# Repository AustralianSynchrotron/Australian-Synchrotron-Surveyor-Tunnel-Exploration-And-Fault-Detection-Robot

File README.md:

Australian-Synchrotron-Surveyor-Tunnel-Exploration-And-Fault-Detection-Robot
=======

Australian Synchrotron Tunnel Bot

###Requirements
------------

1. Python 2.7.x
2. ZeroMQ 3.2.x
3. pyzmq  13.1.0
4. Pyserial
5. libphidget LATEST (currently 2.1.8.20130723)
6. libusb 1.0-0
7. mjpg-streamer experimental
8. cherrypy 3.2.x
9. Arduino 1.5
-- PS2X by Bill Porter
10. supervisor 3.0b2-1
11. ROOter Huntsman 2014-01-25red

###Changes
-------

ipc doesn't seem to be working on this current configuration (except for LCD screen) so motors and IR Sensors using zmq on tcp://127.0.0.2
ports:
irsensor 127.0.0.2:1000
motors 127.0.0.2:1100

note: srv_motor.py now has the bind command for the motors zmq socket, since it is the service which is always running. If testing run py script with sudo

###Command Line
--------

ssh to odroid. The following command line scripts can be used for some low level control of ass-bot

**move** *\<direction\> \<duration\> \<speed\>*

* direction: forward (f), back (b), left (l), right (r)

* duration: time of movement in seconds

* speed: percentage of max speed. From 1 to 100

**shaft** *\<direction\> \<duration\>*

* direction: up (u) or down (d)

* duration: time of movement in seconds

**camera** *\<direction\> \<PWM duration\>*

* direction: Pan (p) or tilt (t)

* PWM duration: Pulse width from 500 to 2500. Form tilt centre value is 900, for pan centre value is 1500

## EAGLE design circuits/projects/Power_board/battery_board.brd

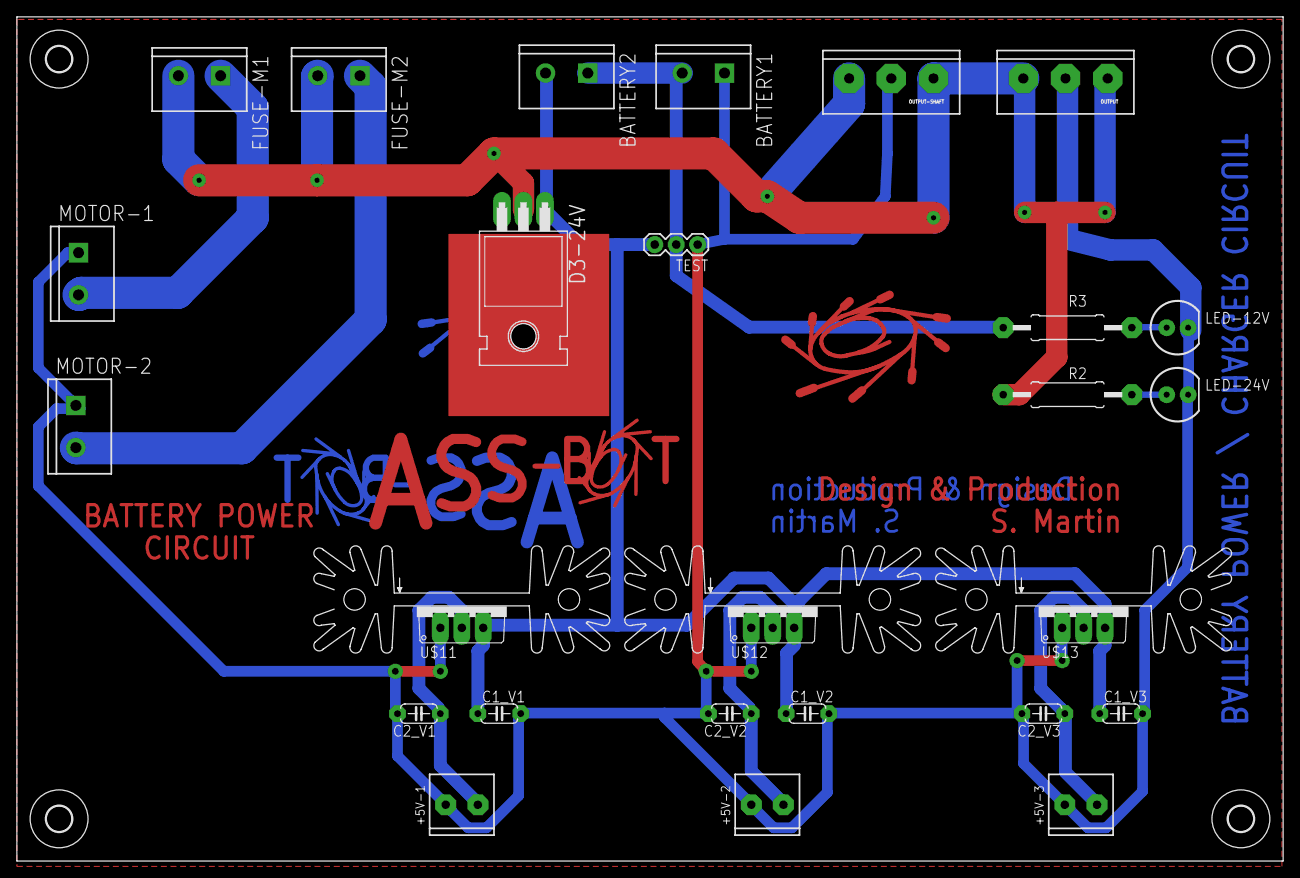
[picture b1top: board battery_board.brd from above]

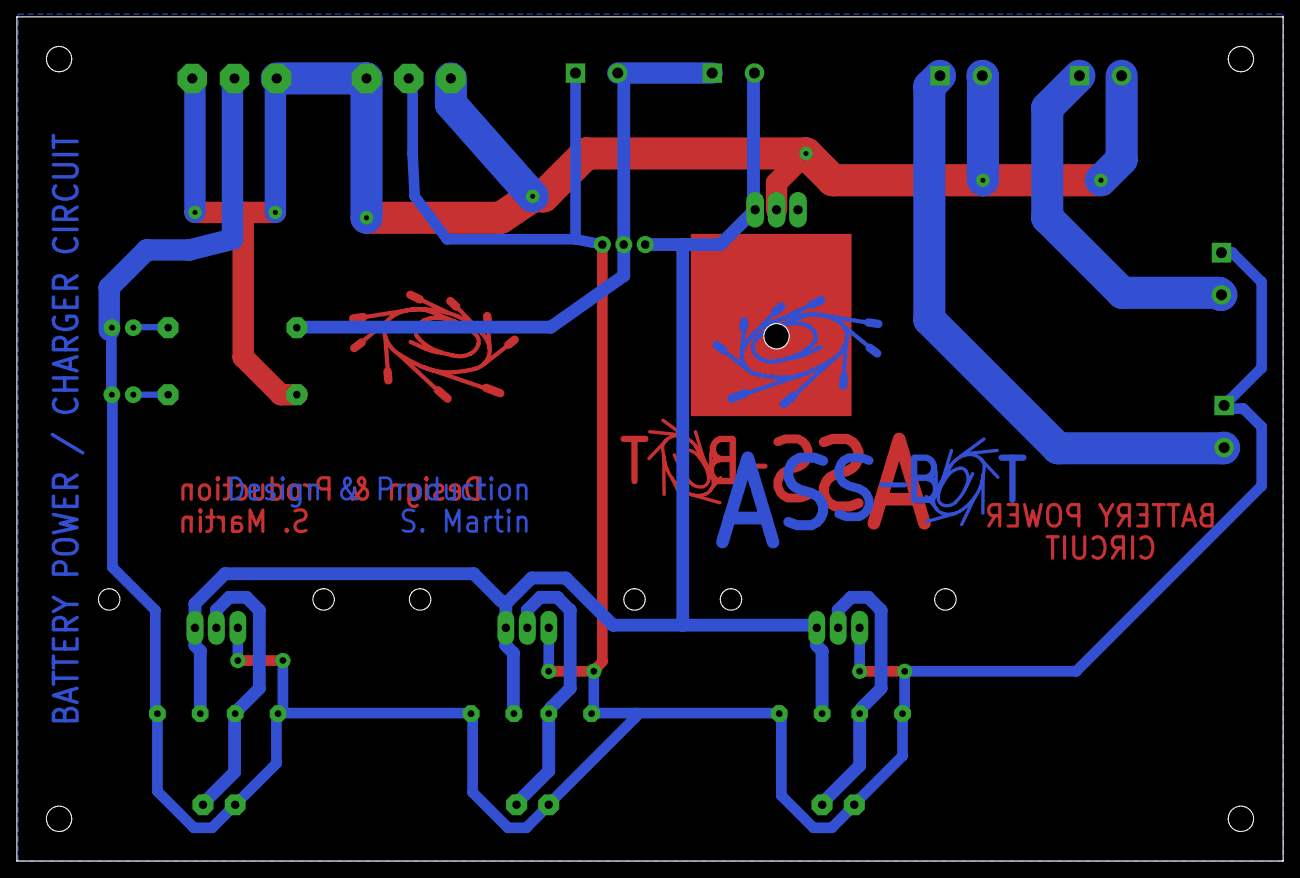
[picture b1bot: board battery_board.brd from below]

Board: 2 copper layers, 150.0 x 100.0 mm, 36 parts (2 on the bottom side), 11 nets.

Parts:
+5V-1, +5V-2, +5V-3: 2-HOLESSC3.81MM; SCREWTERMINAL-3.81MM
BATTERY1, BATTERY2: 12V; SCREWTERMINAL-5MM-2
C1_V1, C1_V2, C1_V3: 2.2uF; C050-024X044
C2_V1, C2_V2, C2_V3: 10uF; C050-024X044
D3-24V: 30A; TO22-DIODE-H
FUSE-M1, FUSE-M2: 3A; SCREWTERMINAL-5MM-2
LED-12V, LED-24V: LED5MM
MOTOR-1, MOTOR-2: 2-HOLESSC5MM; SCREWTERMINAL-5MM-2
OUTPUT: 3-HOLE; SCREWTERMINAL-5MM-3@1
OUTPUT-SHAFT: 3-HOLE; SCREWTERMINAL-5MM-3@1
R2: 1k; 0309/15
R3: 560R; 0309/15
TEST: 1X03
U$1, U$8: LOGO-SYNCHROTRON
U$2: LOGO-ASSBOT-SILK
U$3, U$4, U$5, U$6: 3,0
U$7, U$9: LOGO-ASSBOT
U$10: LOGO-SYNCHROTRON-SILK
U$11, U$12, U$13: LD1085_3A-VREG; TO220V-HEATSINK2

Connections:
12V: BATTERY2.2, C1_V1.1, C1_V2.1, C1_V3.1, D3-24V.P$1, TEST.3, U$11.3, U$12.3, U$13.3
24V: D3-24V.P$2, FUSE-M1.2, FUSE-M2.2, OUTPUT.1, OUTPUT.3, OUTPUT-SHAFT.1, OUTPUT-SHAFT.3, R2.1
GND: +5V-1.1, +5V-2.1, +5V-3.1, BATTERY1.1, C1_V1.2, C1_V2.2, C1_V3.2, C2_V1.2, C2_V2.2, C2_V3.2, LED-12V.K, LED-24V.K, MOTOR-1.1, MOTOR-2.1, OUTPUT.2, OUTPUT-SHAFT.2, TEST.1, U$11.1, U$12.1, U$13.1
unnamed: LED-24V.A, R2.2
unnamed: BATTERY1.2, BATTERY2.1, R3.1, TEST.2
unnamed: +5V-3.2, C2_V3.1, U$13.2
unnamed: FUSE-M2.1, MOTOR-2.2
unnamed: FUSE-M1.1, MOTOR-1.2
unnamed: LED-12V.A, R3.2
unnamed: +5V-2.2, C2_V2.1, U$12.2
unnamed: +5V-1.2, C2_V1.1, U$11.2

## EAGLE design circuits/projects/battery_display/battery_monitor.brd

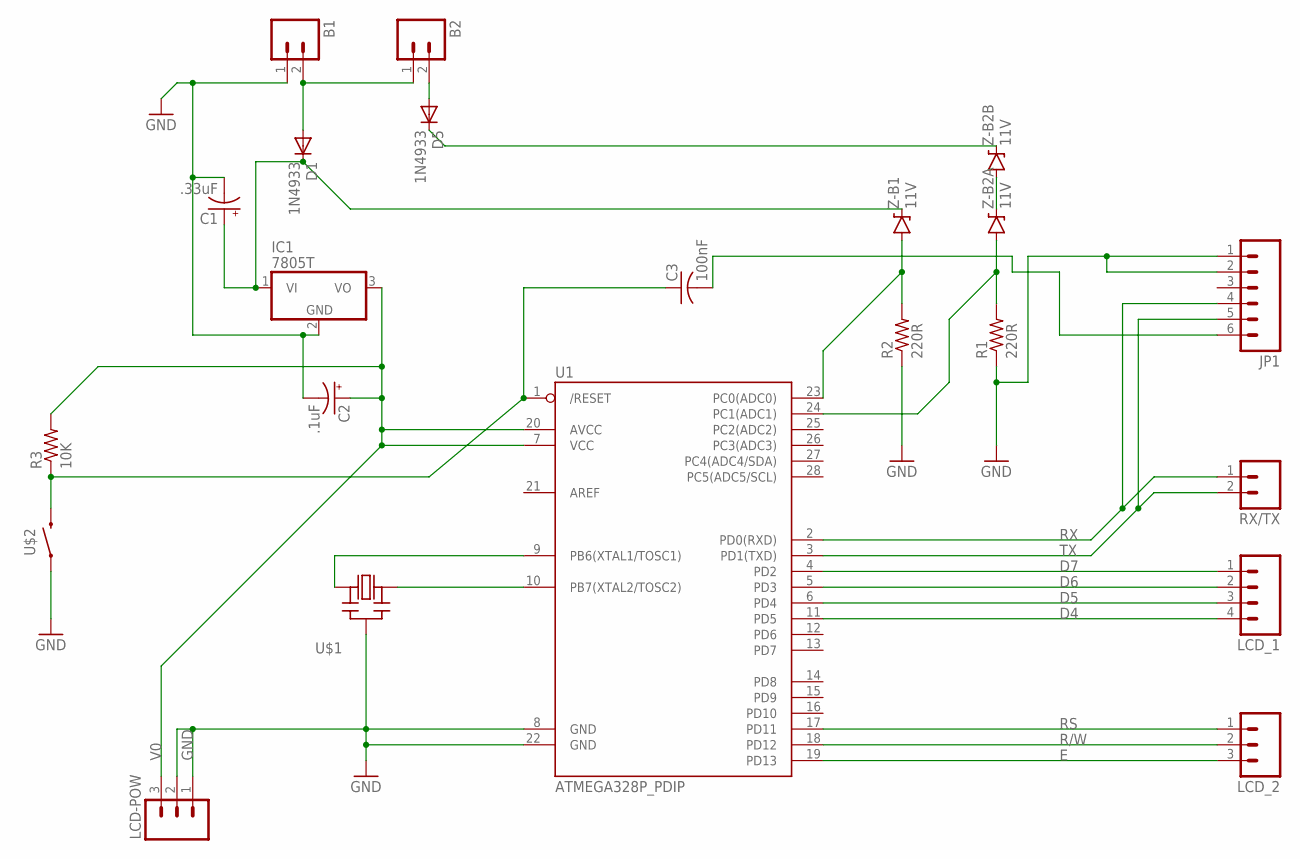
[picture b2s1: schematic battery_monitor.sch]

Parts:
B1, B2: 2-HOLES2-HOLES-5.08MM; 2-HOLES_BIG
C1: .33uF; E2,5-5
C2: .1uF; E2,5-5
C3: 100nF; C050-025X075
D1, D5: 1N4933; DO41-10
IC1: 7805T; TO220H
JP1: M06LONGPADS; 1X06_LONGPADS
LCD-POW: M03PTH; 1X03
LCD_1: M04PTH; 1X04
LCD_2: M03PTH; 1X03
R1, R2: 220R; 0207/10
R3: 10K; 0207/10
RX/TX: M02PTH; 1X02
U1: ATMEGA328P_PDIP; DIL28-3
U$1: OSCILLATOR-THM; CERM_OSC
U$2: SWITCH-MOMENTARY4MM; TACTILE_SWITCH_SMD
Z-B1, Z-B2A, Z-B2B: 11V; DIODE-ZENER

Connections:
D4: LCD_1.4, U1.11 (PD5)
D5: LCD_1.3, U1.6 (PD4)
D6: LCD_1.2, U1.5 (PD3)
D7: LCD_1.1, U1.4 (PD2)
E: LCD_2.3, U1.19 (PD13)
GND: B1.1, C1.-, C2.-, IC1.2 (GND), JP1.1, JP1.2, LCD-POW.1, LCD-POW.2, R1.1, R2.1, U1.8 (GND), U1.22 (GND), U$1.P$2 (GND), U$2.1, U$2.2 (1)
unnamed: U1.10 (PB7(XTAL2/TOSC2)), U$1.P$3 (OUT)
unnamed: U1.9 (PB6(XTAL1/TOSC1)), U$1.P$1 (IN)
unnamed: B1.2, B2.1, D1.A
unnamed: C1.+, D1.C, IC1.1 (VI), Z-B1.P$1 (C)
unnamed: Z-B2A.P$1 (C), Z-B2B.P$2 (A)
unnamed: C3.1, R3.1, U1.1 (/RESET), U$2.3 (2), U$2.4 (2)
unnamed: C3.2, JP1.6
unnamed: R2.2, U1.23 (PC0(ADC0)), Z-B1.P$2 (A)
unnamed: R1.2, U1.24 (PC1(ADC1)), Z-B2A.P$2 (A)
unnamed: D5.C, Z-B2B.P$1 (C)
unnamed: B2.2, D5.A
R/W: LCD_2.2, U1.18 (PD12)
RS: LCD_2.1, U1.17 (PD11)
RX: JP1.4, RX/TX.1, U1.2 (PD0(RXD))
TX: JP1.5, RX/TX.2, U1.3 (PD1(TXD))
V0: C2.+, IC1.3 (VO), LCD-POW.3, R3.2, U1.7 (VCC), U1.20 (AVCC)

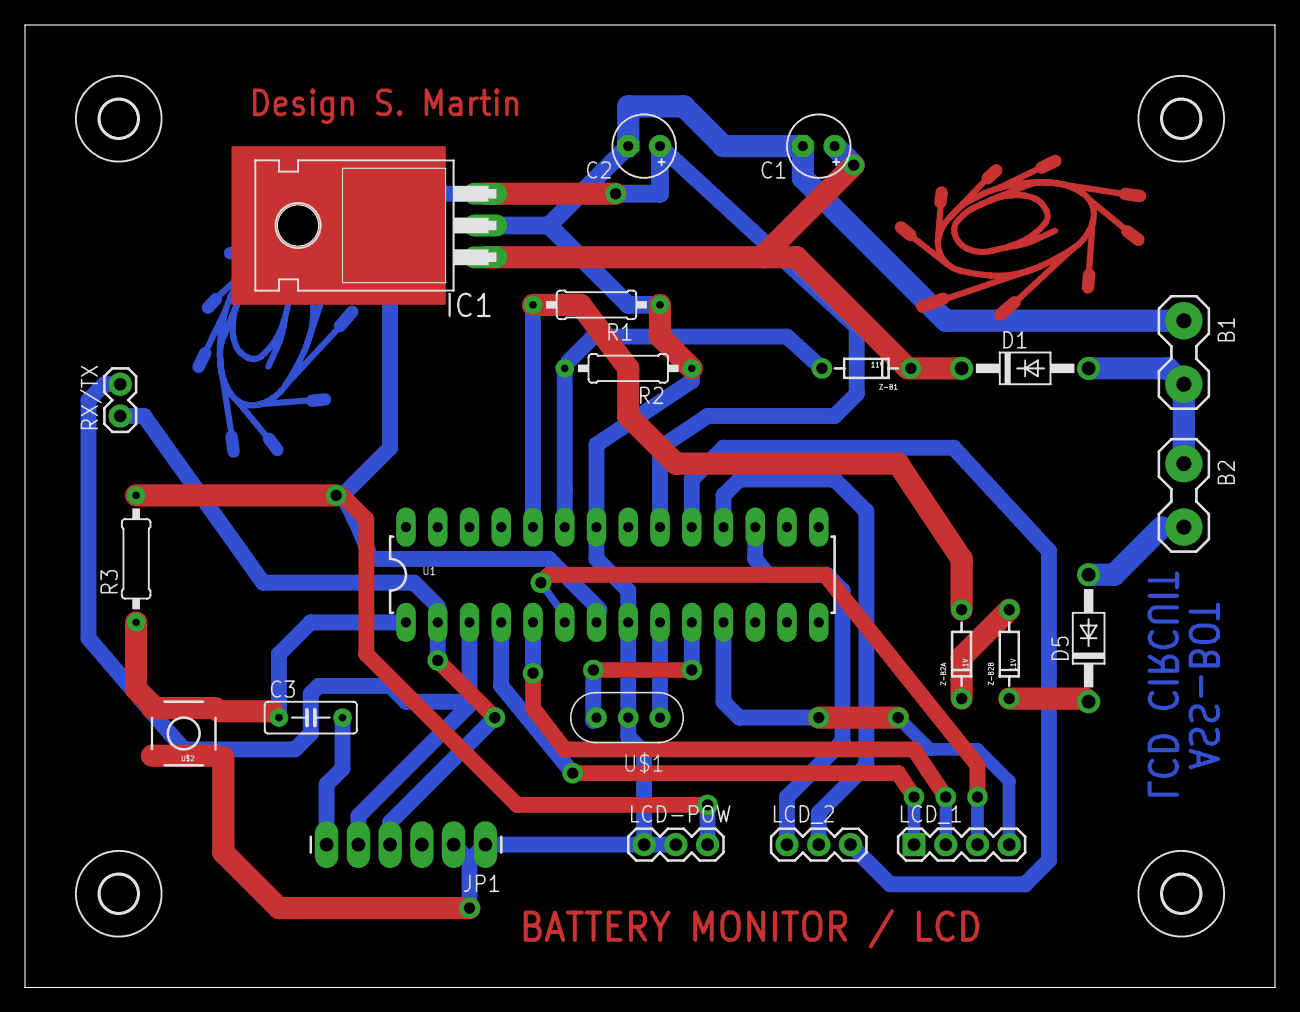
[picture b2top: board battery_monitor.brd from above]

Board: 2 copper layers, 100.0 x 77.0 mm, 28 parts (1 on the bottom side), 22 nets.

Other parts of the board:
U$3, U$4, U$5, U$6: 3,0
U$7, U$8: LOGO-SYNCHROTRON

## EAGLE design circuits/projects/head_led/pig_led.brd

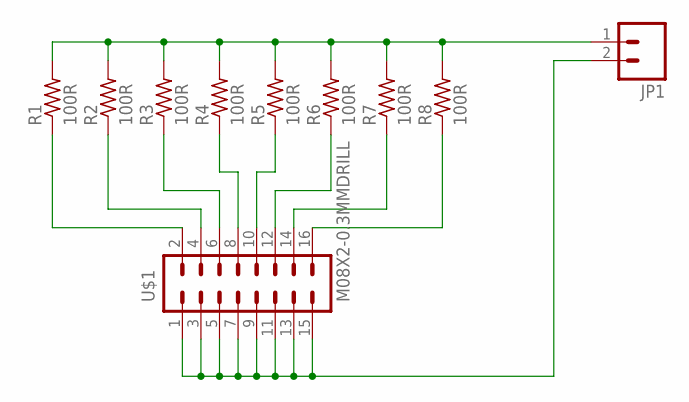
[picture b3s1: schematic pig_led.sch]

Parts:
JP1: M023.5MM; SCREWTERMINAL-3.5MM-2
R1, R2, R3, R4, R5, R6, R7, R8: 100R; 0207/10
U$1: M08X2-0.3MMDRILL; 2X8

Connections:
GND: JP1.2, U$1.1, U$1.3, U$1.5, U$1.7, U$1.9, U$1.11, U$1.13, U$1.15
unnamed: R1.1, U$1.2
unnamed: R2.1, U$1.4
unnamed: R3.1, U$1.6
unnamed: R4.1, U$1.8
unnamed: R5.1, U$1.10
unnamed: R6.1, U$1.12
unnamed: R7.1, U$1.14
unnamed: R8.1, U$1.16
VCC: JP1.1, R1.2, R2.2, R3.2, R4.2, R5.2, R6.2, R7.2, R8.2

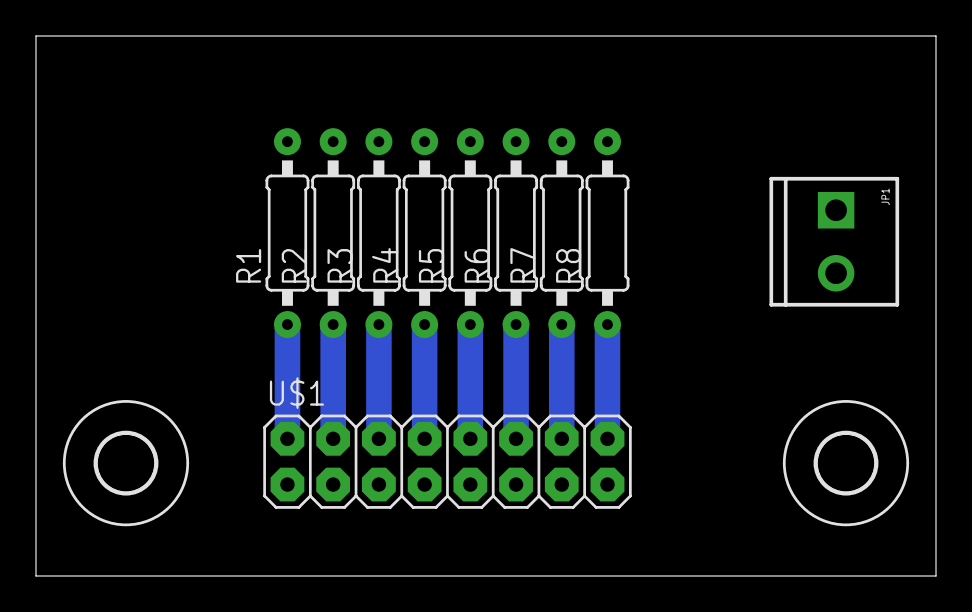
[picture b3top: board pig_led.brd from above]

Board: 2 copper layers, 50.0 x 30.0 mm, 12 parts (0 on the bottom side), 10 nets.

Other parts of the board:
U$2, U$3: 3,2

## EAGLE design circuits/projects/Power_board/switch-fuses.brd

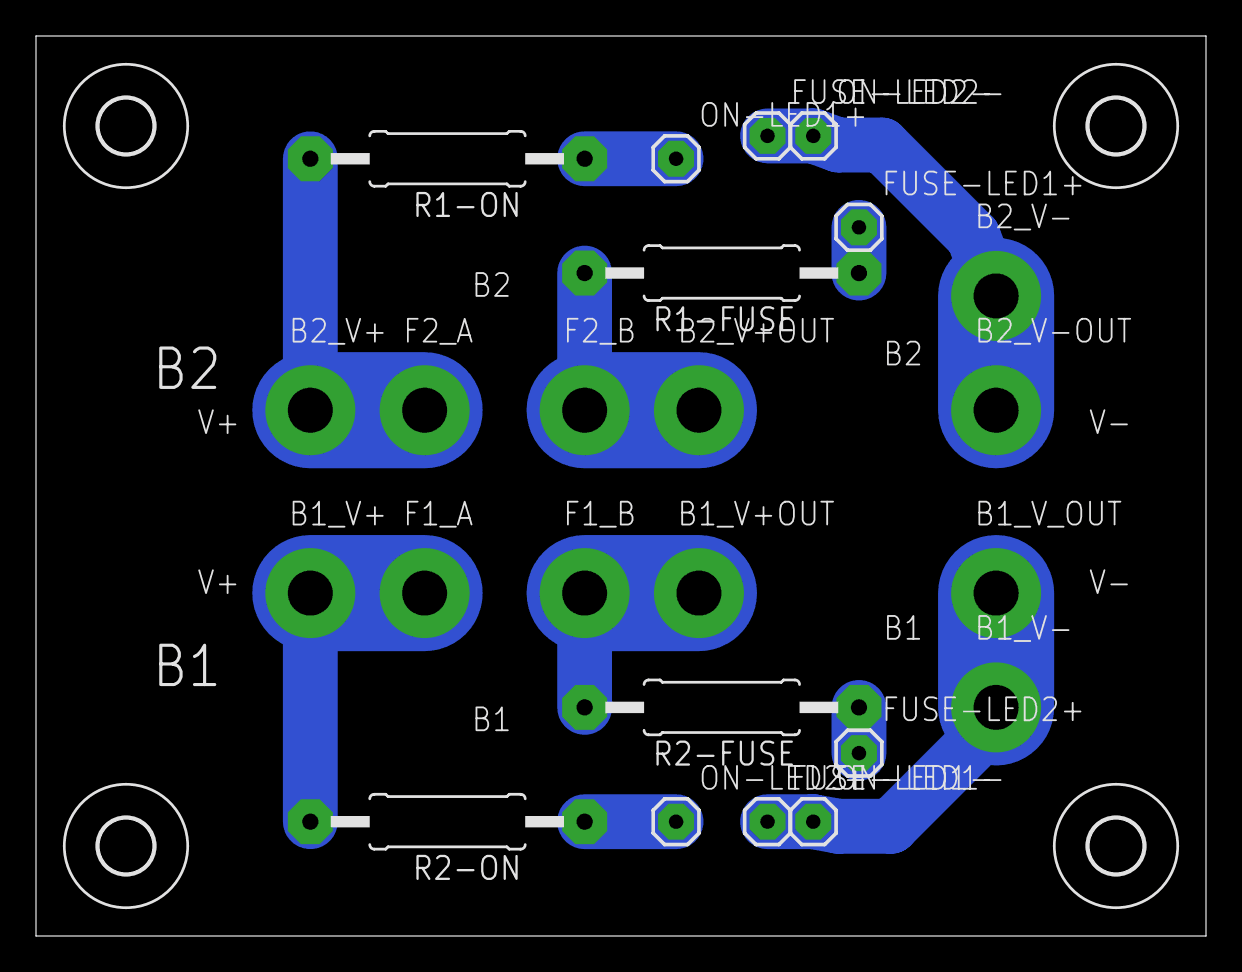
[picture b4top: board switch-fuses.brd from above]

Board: 2 copper layers, 65.0 x 50.0 mm, 28 parts (0 on the bottom side), 10 nets.

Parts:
B1_V+, B1_V+OUT, B1_V-, B1_V_OUT, B2_V+, B2_V+OUT, B2_V-, B2_V-OUT: 1-HOLE2.5MM; 1-HOLE-2.5MM
F1_A, F1_B, F2_A, F2_B: 1-HOLE2.5MM; 1-HOLE-2.5MM
FUSE-LED1+, FUSE-LED1-, FUSE-LED2+, FUSE-LED2-: 1-HOLE0.8MM; 1-HOLE
ON-LED1+, ON-LED1-, ON-LED2+, ON-LED2-: 1-HOLE0.8MM; 1-HOLE
R1-FUSE, R1-ON, R2-FUSE, R2-ON: 560R; 0309/15
U$1, U$2, U$3, U$4: 3,0

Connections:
unnamed: FUSE-LED1+.1, R1-FUSE.1
unnamed: FUSE-LED2+.1, R2-FUSE.1
unnamed: ON-LED1+.1, R1-ON.1
unnamed: ON-LED2+.1, R2-ON.1
V+1: B2_V+OUT.P$1, F2_B.P$1, R1-FUSE.2
V+2: B1_V+OUT.P$1, F1_B.P$1, R2-FUSE.2
V-1: B1_V-.P$1, B1_V_OUT.P$1, FUSE-LED1-.1, ON-LED1-.1
V-2: B2_V-.P$1, B2_V-OUT.P$1, FUSE-LED2-.1, ON-LED2-.1
VIN1: B1_V+.P$1, F1_A.P$1, R2-ON.2
VIN2: B2_V+.P$1, F2_A.P$1, R1-ON.2

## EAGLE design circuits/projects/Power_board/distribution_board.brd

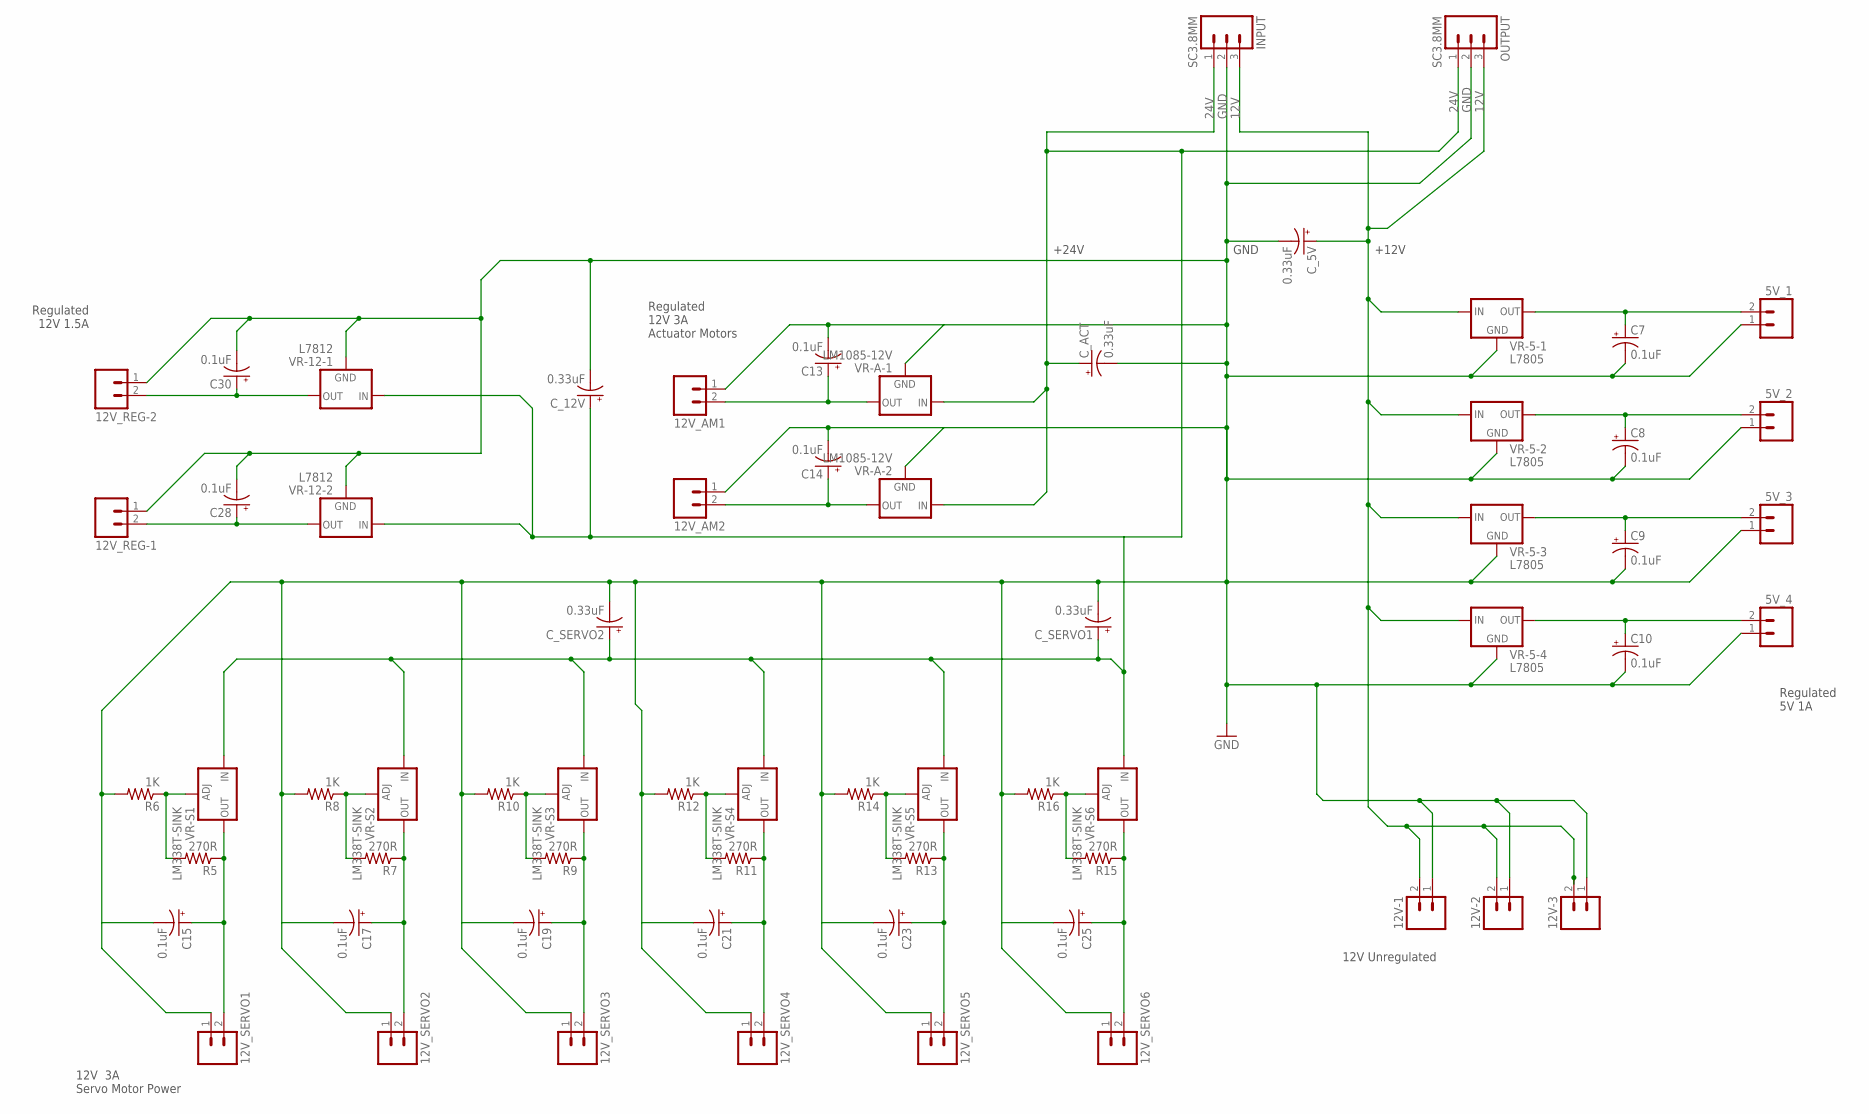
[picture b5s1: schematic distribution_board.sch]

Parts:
5V_1, 5V_2, 5V_3, 5V_4, 12V-1, 12V-2, 12V-3, 12V_AM1, 12V_AM2, 12V_REG-1, 12V_REG-2, 12V_SERVO1, 12V_SERVO2, 12V_SERVO3, 12V_SERVO4, 12V_SERVO5, 12V_SERVO6: SC3.81MM; SCREWTERMINAL-3.81MM
C7, C8, C9, C10, C13, C14, C15, C17, C19, C21, C23, C25, C28, C30: 0.1uF; E2,5-5
C_5V, C_12V: 0.33uF; E2,5-5
C_ACT: 0.33uF; E2,5-5
C_SERVO1, C_SERVO2: 0.33uF; E2,5-5
INPUT: SC3.8MM; SCREWTERMINAL-5MM-3
OUTPUT: SC3.8MM; SCREWTERMINAL-5MM-3
R5, R7, R9, R11, R13, R15: 270R; 0207/2V
R6, R8, R10, R12, R14, R16: 1K; 0207/2V
VR-5-1, VR-5-2, VR-5-3, VR-5-4: L7805; TO263
VR-12-1, VR-12-2: L7812; TO263
VR-A-1, VR-A-2: LM1085-12V; TO220V-HEATSINK
VR-S1, VR-S2, VR-S3, VR-S4, VR-S5, VR-S6: LM338T-SINK; TO220V-HEATSINK

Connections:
12V: 12V-1.2, 12V-2.2, 12V-3.2, C_5V.+, INPUT.3, OUTPUT.3, VR-5-1.1 (IN), VR-5-2.1 (IN), VR-5-3.1 (IN), VR-5-4.1 (IN)
24V: C_12V.+, C_ACT.+, C_SERVO1.+, C_SERVO2.+, INPUT.1, OUTPUT.1, VR-12-1.1 (IN), VR-12-2.1 (IN), VR-A-1.3 (IN), VR-A-2.3 (IN), VR-S1.3 (IN), VR-S2.3 (IN), VR-S3.3 (IN), VR-S4.3 (IN), VR-S5.3 (IN), VR-S6.3 (IN)
GND: 5V_1.1, 5V_2.1, 5V_3.1, 5V_4.1, 12V-1.1, 12V-2.1, 12V-3.1, 12V_AM1.1, 12V_AM2.1, 12V_REG-1.1, 12V_REG-2.1, 12V_SERVO1.1, 12V_SERVO2.1, 12V_SERVO3.1, 12V_SERVO4.1, 12V_SERVO5.1, 12V_SERVO6.1, C7.-, C8.-, C9.-, C10.-, C13.-, C14.-, C15.-, C17.-, C19.-, C21.-, C23.-, C25.-, C28.-, C30.-, C_5V.-, C_12V.-, C_ACT.-, C_SERVO1.-, C_SERVO2.-, INPUT.2, OUTPUT.2, R6.2, R8.2, R10.2, R12.2, R14.2, R16.2, VR-5-1.3 (GND), VR-5-2.3 (GND), VR-5-3.3 (GND), VR-5-4.3 (GND), VR-12-1.3 (GND), VR-12-2.3 (GND), VR-A-1.1 (GND), VR-A-2.1 (GND)
unnamed: 12V_REG-1.2, C28.+, VR-12-2.2 (OUT)
unnamed: 5V_1.2, C7.+, VR-5-1.2 (OUT)
unnamed: 5V_2.2, C8.+, VR-5-2.2 (OUT)
unnamed: 5V_3.2, C9.+, VR-5-3.2 (OUT)
unnamed: 5V_4.2, C10.+, VR-5-4.2 (OUT)
unnamed: 12V_AM1.2, C13.+, VR-A-1.2 (OUT)
unnamed: 12V_AM2.2, C14.+, VR-A-2.2 (OUT)
unnamed: R5.2, R6.1, VR-S1.1 (ADJ)
unnamed: 12V_REG-2.2, C30.+, VR-12-1.2 (OUT)
unnamed: 12V_SERVO1.2, C15.+, R5.1, VR-S1.2 (OUT)
unnamed: 12V_SERVO2.2, C17.+, R7.1, VR-S2.2 (OUT)
unnamed: R7.2, R8.1, VR-S2.1 (ADJ)
unnamed: 12V_SERVO3.2, C19.+, R9.1, VR-S3.2 (OUT)
unnamed: R9.2, R10.1, VR-S3.1 (ADJ)
unnamed: 12V_SERVO4.2, C21.+, R11.1, VR-S4.2 (OUT)
unnamed: R11.2, R12.1, VR-S4.1 (ADJ)
unnamed: 12V_SERVO5.2, C23.+, R13.1, VR-S5.2 (OUT)
unnamed: R13.2, R14.1, VR-S5.1 (ADJ)
unnamed: 12V_SERVO6.2, C25.+, R15.1, VR-S6.2 (OUT)
unnamed: R15.2, R16.1, VR-S6.1 (ADJ)

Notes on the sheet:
+24V
+12V
GND
Regulated 5V 1A
Regulated 12V 3A Actuator Motors
12V 3A Servo Motor Power
Regulated 12V 1.5A
12V Unregulated

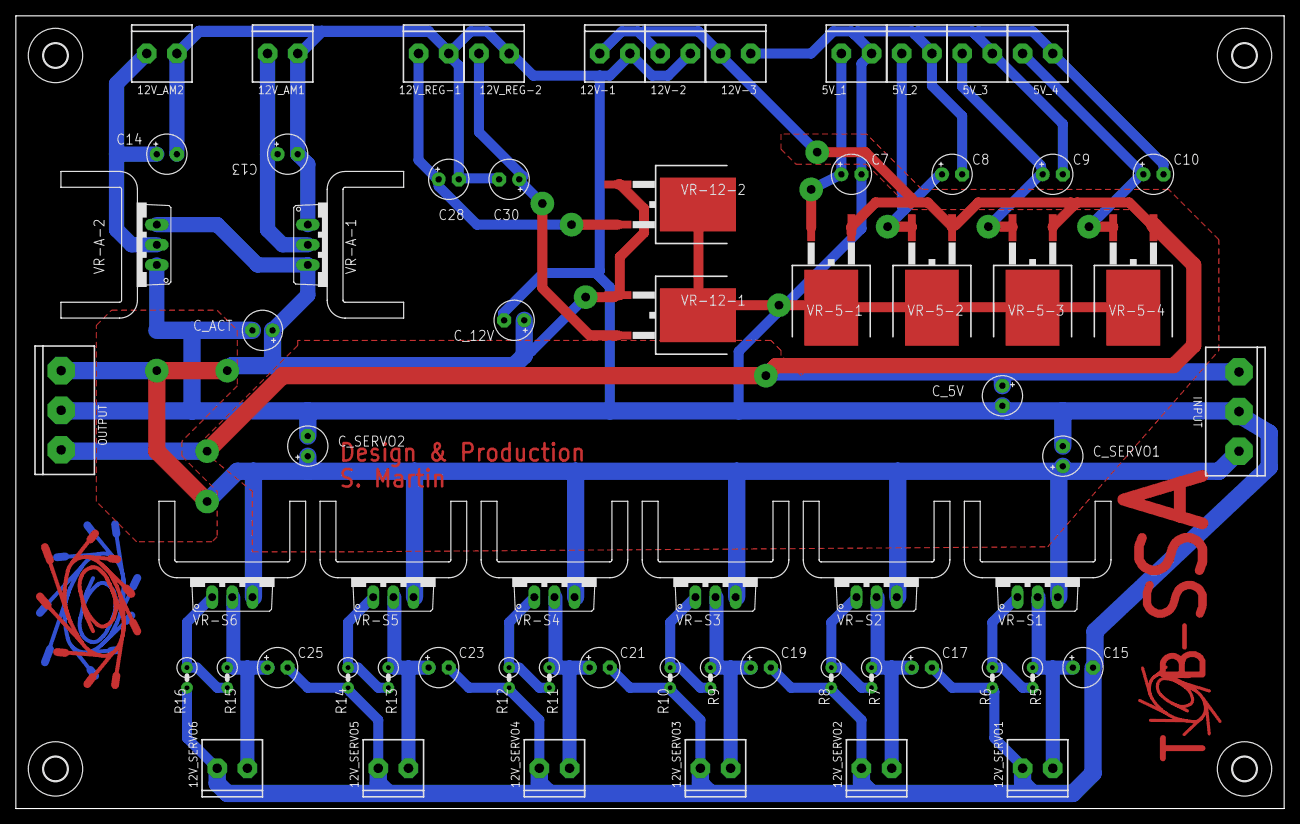
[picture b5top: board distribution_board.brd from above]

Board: 2 copper layers, 160.0 x 100.0 mm, 72 parts (1 on the bottom side), 23 nets.

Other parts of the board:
U$2, U$4: LOGO-SYNCHROTRON
U$3: LOGO-ASSBOT
U$5: LOGO-ASSBOT-SILK
U$6, U$7, U$8, U$9: 3,0

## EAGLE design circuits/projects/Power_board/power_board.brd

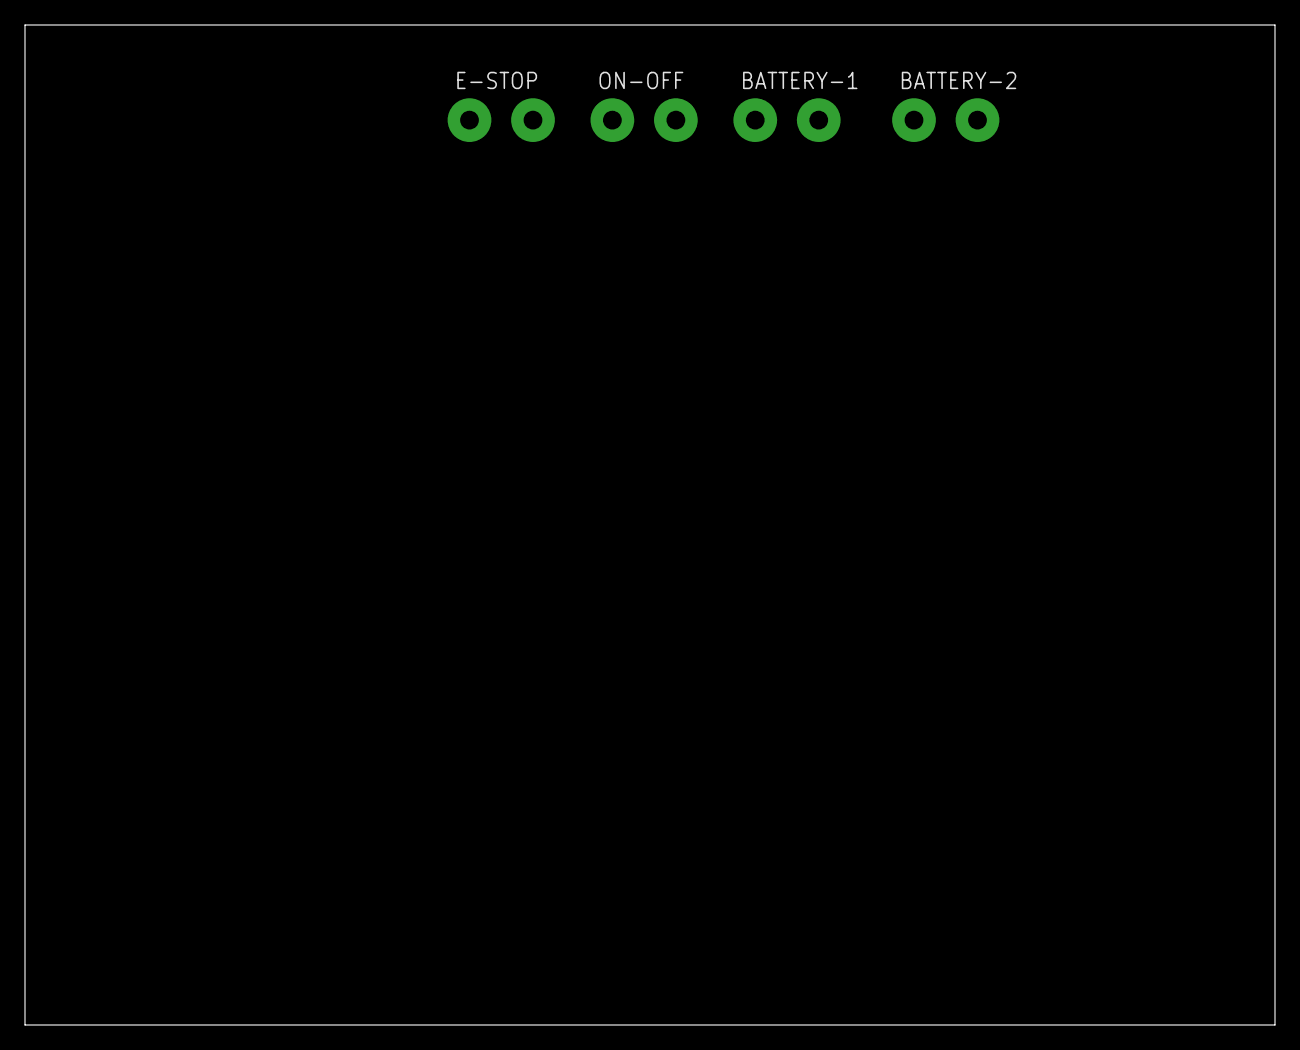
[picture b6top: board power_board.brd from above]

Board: 2 copper layers, 100.0 x 80.0 mm, 4 parts (0 on the bottom side), 3 nets, no tracks yet.

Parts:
BATTERY-1, BATTERY-2: 1X02_1.5M_HOLES
E-STOP: 2-PIN-SWITCH2X1.5MM_HOLES; 1X02_1.5M_HOLES
ON-OFF: 2-PIN-SWITCH2X1.5MM_HOLES; 1X02_1.5M_HOLES

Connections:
unnamed: BATTERY-1.2, BATTERY-2.1
unnamed: E-STOP.2, ON-OFF.1
VCC: BATTERY-1.1, ON-OFF.2

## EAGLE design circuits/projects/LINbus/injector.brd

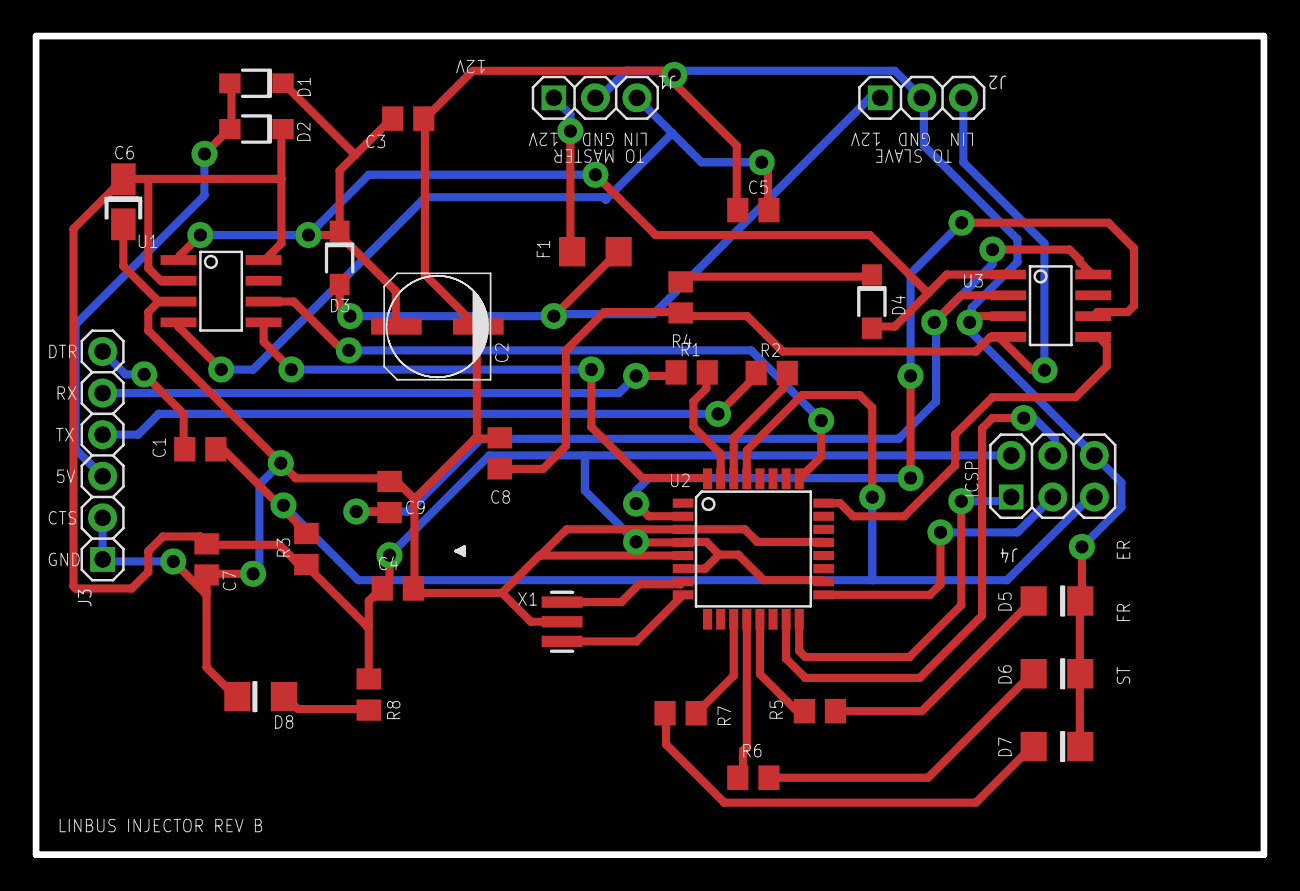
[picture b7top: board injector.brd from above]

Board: 2 copper layers, 75.0 x 50.0 mm, 34 parts (0 on the bottom side), 32 nets.

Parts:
C1, C4, C7, C9: 0.1uF; C0805
C2: 22uF 40V; UD-6,3X5,8_NICHICON
C3: 0.1uF 50V; C0805
C5, C8: 220pF; C0805
C6: 10uF; A/3216-18R
D1, D2, D3, D4: MBR0540; SOD123FL
D5: RED; 1206-LED
D6, D7: GREEN; 1206-LED
D8: BLUE; 1206-LED
F1: 500ma Slow; 1206
J1, J2: 1X03
J3: 1X06
J4: ICSP; 2X03
R1, R2: 10K; R0805
R3: 10k; R0805
R4: 1K; R0805
R5, R6, R7, R8: 3.3K; R0805
U1, U3: ATA6631; SO-08
U2: ATMEGA328; TQFP32-08
X1: 16MHz; RESONATOR-SMD

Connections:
+5V: C4.1, C6.+, C7.1, D2.C, J4.2, R3.1, R8.2, U1.2, U1.8, U2.4, U2.6, U2.18
+12V: C2.+, C3.1, D1.C, D3.C, D4.A, U1.1, U3.1
DTR: C1.1, J3.6
ERROR_LED: R5.2, U2.13
FRAME_LED: R6.2, U2.12
GND: C2.-, C3.2, C4.2, C5.2, C6.-, C7.2, C8.2, C9.2, D5.C, D6.C, D7.C, D8.C, J1.2, J2.2, J3.1, J3.2, J4.6, U1.3, U2.3, U2.5, U2.21, U3.3, X1.2
LIN1: C5.1, J1.3, U1.4
LIN1_RX: U1.5, U2.32
LIN1_TX: U1.6, U2.25
LIN2: C8.1, J2.3, R4.2, U3.4
LIN2_RX: U2.24, U3.5
LIN2_TX: U2.2, U3.6
MISO/LIN_DATA: J4.1, U2.16
MOSI/LIN_ERR: J4.4, U2.15
unnamed: D7.A, R7.1
unnamed: D8.A, R8.1
unnamed: D6.A, R6.1
unnamed: D5.A, R5.1
unnamed: D3.A, F1.2, J2.1
unnamed: D4.C, R4.1
RESET: C1.2, J4.5, R3.2, U2.29
RXI: J3.5, R1.2
S-5V: D1.A, D2.A, J3.3
SCK: J4.3, U2.17
SECONDARY_5V: C9.1, U3.2, U3.8
SER_RX: R2.1, U2.30
SER_TX: R1.1, U2.31
STATUS_LED: R7.2, U2.11
TXO: J3.4, R2.2
VBAT: F1.1, J1.1
XTAL1: U2.7, X1.3
XTAL2: U2.8, X1.1

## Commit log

2013-10-03 Improved comments and implemented interupt handler to cleanly shut down
2013-10-06 Donkey Logo
2013-10-06 RoboDonkey Logo
2013-10-20 Changed motor mount method
2013-11-03 CNC mill cutout drawings for wood baseplate
2013-11-06 made eagle library for circuit board
2013-11-06 circuit board work
2013-11-06 board work
2013-11-14 circuits and charger plans
2013-11-15 circuit boards
2013-11-15 logo
2013-11-15 board for circuit
2013-11-15 various dxf formats for the eagle
2013-11-15 logo in eagle library
2013-11-15 battery board made
2013-11-16 Arduino code for remote control with PS2 controller
2013-11-16 Updated arduino requirements
2013-11-16 general update of drawings
2013-11-16 new board and some ignores
2013-11-17 initial remote control cherrypy server
2013-11-17 gittin the night away
2013-11-17 ignore file
2013-11-18 Trying to get the POST requests working
2013-11-20 new fuse clip
2013-11-29 arduino remote control interface POSTing
2013-12-01 adding zmq support
2013-12-02 first board finished
2013-12-02 fixed board error
2013-12-02 Revert "fixed board error"
    This reverts commit a9d72898da9c7dfbc8182aee948ad086d6644fb1.
2013-12-02 new switch and fuse circuit
2013-12-03 configured zmq message string from arduino
2013-12-03 updated requirements
2013-12-03 variablised hardcoded numbers
2013-12-04 more datasheets
2013-12-14 Updated autostart and added files to supervisor config
2013-12-14 Changed IP's for production box
2013-12-15 updated arduino for production
2013-12-15 Tried to add image stream to main page... tried...
2013-12-15 Second time lucky... embedded streaming image
2013-12-16 Debugging messages being passed
2013-12-17 add some shit
2013-12-17 made board tracks bigger
2014-01-05 new shit
2014-01-16 removed
2014-01-19 renamed lcd datasheet correctly
2014-01-28 Trying to debug network communication, seems to be an motors.ipc issue
2014-01-28 debugging network communication
    The ps2 controller and arduino (freetronics) are talking over the
    network and the message is getting to the robot via the cherrypy
    webserver. The message doesn't seem to be getting passed through the
    motors.ipc to the motors server... They are receiving a message of 0...
2014-01-28 changed back to the push pull message format
2014-02-15 fixed motor code - acceleration value problem
2014-02-18 fixed motor code
2014-02-19 Removed delays used during debugging
2014-02-19 new datasheets
2014-02-25 Changes for new OS
2014-02-25 Steps to set up Ubuntu 13.10 whisper odroid image
2014-02-25 added mpstat (sysstat) for processor statistics
2014-03-04 Create openwrt-install
2014-03-04 Update openwrt-install
2014-03-19 assbot panel
2014-03-20 back up of ROOter config files, for client bridge operation of tl mr-3420 v2.3
2014-03-20 added router firmware requirements
2014-03-21 trying to get video streaming working, WIP
2014-03-22 mapped video14 to videoA to work with uvc commands
2014-03-22 added note about udev rules for webcam
2014-03-23 small changes + added mode string
2014-03-23 added mode option for different controllers
2014-03-23 modified for local server changes
2014-03-23 fix problems with the dead band
2014-03-23 fixed motor controller directions
2014-03-23 increased the central deadband to prevent jerky movement at rest...
2014-03-24 added a standard 25% change in acceleration
2014-03-24 Create sensor-mounting-bracket.stl
    Trying to design a 3d printable model that can slip over the aluminium extrusion in order to mount sensors at any location around the extremity
2014-03-24 3d sensor clip
2014-03-24 corrupted file
2014-03-24 revised thing
2014-03-25 Unable to be loaded into MakerWare
2014-03-25 Minor hole adjustments
2014-03-25 ignore 3d modelling temp files
2014-03-25 3d design of a 45 degree sensor mount
2014-03-25 minor change to reduce deformities on clip
2014-03-27 built some shit for main power panel
2014-04-02 more ass-work done
2014-04-02 battery monitor sketch
2014-04-04 new fan clip design
2014-04-04 git is stuffed
2014-04-04 resaved a thing
2014-04-04 test spring for test print
2014-04-04 Updated to fit within print area
2014-04-05 more parts to print... jump on the band wagon!
2014-04-06 Ride that horse
2014-04-06 connector for extrusion
2014-04-06 Changed orientation to improve print performance
2014-04-06 Trying to debug zmq subscribe problem - added extra debug info
2014-04-11 using tcp for zmq as workaround
2014-04-14 git. git git gitgit. git
2014-04-15 ass-monitor code for battery installed
2014-04-16 socket debugging
2014-04-16 try to solve startup issues for remote_control
2014-04-17 reverted tcp changes, problem seemed to be file permissions
2014-04-17 reordered left and right controls
2014-04-22 added full left/right, 50% acceleration
2014-04-22 initial attempt to make a web control interface
2014-04-22 new web control files
2014-04-30 prototype drawings
2014-05-01 added js gauges and fixed file references
2014-06-10 baseplate
2014-06-24 pan tilt mechanism for micro servos
2014-06-26 Updated model after first print
2014-06-27 minor modifications after 2nd print
2014-07-09 linbus circuits
2014-07-12 Poorly Rooted V1
2014-07-13 45degree joint bracket for body work
2014-07-16 LED board for pig head
2014-07-17 pig skull led board complete
2014-07-19 pig head temporary brackets
2014-07-22 created a mirror on the wall
2014-07-23 3d printer calibration objects
2014-07-24 test mounting plate for shafting
2014-07-27 added some extra brackets to join the frame
2014-07-27 Cover Pieces for laser cutting c/o Louise
2014-08-06 switch brackets
2014-08-11 3d model for snap dragons
2014-08-11 modifications after print to better fit frame
2014-08-14 new boards
2014-09-02 make body bracket drawings
2014-09-09 some boards updated
2014-09-11 yeah
2014-10-01 srduino code for ultrasounds
2014-10-06 refined drawing for full size template
2014-10-07 Redraw of pan tilt for metal fabrication
2014-10-22 woowoooo
2014-10-23 update lib
2014-10-23 board
2014-10-23 wooo
2014-10-29 stuff
2014-10-30 upload in progress files after hiatus
2014-10-30 updated for new ip
2014-10-30 trying to get some socketio action happening for more responsive control and readback
2014-11-01 top plate platters for machining
2014-11-01 removed files for pycharm
2014-11-03 inserted callbacks for bump sensors and bumper.ipc for comms
2014-11-11 circuits
2014-11-24 some updates
2014-11-26 commit that shit
2014-12-04 zippity boo
2015-01-25 trying to get servo control working - no errors
2015-01-25 test app up and running
2015-01-26 updates for flask webserver testing
2015-01-26 eripower module datasheets
2015-02-07 added service script to run webservice
2015-02-07 fixed errors and added nice colours and formatting
2015-02-07 removed battery socket
2015-02-07 moved motor control to use WebService
2015-02-07 moved battery reading to WebService to allow for mulitple connections to each motor
2015-02-07 udev rules to make phidgets user writable
2015-02-07 added phidgets webservice with logging
2015-02-07 various minor changes
2015-02-07 trying to get battery voltage messages passed to webpage, replaced tabs with spaces
2015-02-07 fixed battery status json
2015-02-08 added flask dev server for socketio
2015-02-08 basic socketio battery reporting
2015-02-08 added streaming image to display
2015-02-08 removed redundant backend signal references
2015-02-08 Implemented battery dial gauges linked via socketIO
2015-02-08 battery states of charge for reference
2015-02-08 added charging state to display
2015-02-08 changed dial colour scheme, blue=charging, green=normal, yellow=warning, red=danger
2015-02-09 added time running on battery
2015-02-09 moved time on battery calc to odroid to avoid time zone diffs
2015-02-09 adjusted layout of battery data
2015-02-09 new static folder and files for flask remotecontrol server
2015-02-09 images for bump detection display
2015-02-09 some extra images to get a nice layout
2015-02-09 added display framework for bumper components
2015-02-17 added fractional number format following ticket#16
2015-02-18 added some scripts for supervisor integration
2015-02-18 added reboot and kill server to supervisor
2015-02-19 adding framework for bump sensors display
2015-02-20 debugging bumper socket.io
2015-02-20 fixed problems with recv_json hanging/ waiting for a message
2015-02-20 fleshed out bumper details
2015-02-23 end of shift changes
2015-03-23 fiddling with my shaft control...
2015-03-29 some drawings
2015-04-02 trying to get shaft moving, but sweet nothings not heard
2015-04-02 removed code that might prevent ip being displayed on next start up
2015-04-02 added shutdown script for supervised shutdowns
2015-04-19 updated data frame to include up down shaft
2015-04-19 moved devices to webservice connected and PUB/SUB sockets
2015-04-19 successful testing of shaft operation
2015-04-19 updated to call function from command line
2015-04-19 updated shaft code to match test suite
2015-04-19 added shaft to supervisor/ cleaned up code
2015-05-08 deleted some
2015-05-10 fixed bugs in srv_shaft/ updated IR to remote open/ tweaked config
2015-05-10 uploaded odroids working sauce code
2015-05-10 added servo code
2015-05-10 update supevisor
2015-05-10 change user for shaft and motor server
2015-05-10 started scripts for command line controls
2015-05-10 Add controls scripts
2015-05-11 updated controls
2015-05-12 ipython added shaft
2015-06-06 new switch holder. longer delay on ultrasound arduino code
2016-01-31 clean up files on bot/ previously chnaged files
2017-04-13 minor update to server address and ports
